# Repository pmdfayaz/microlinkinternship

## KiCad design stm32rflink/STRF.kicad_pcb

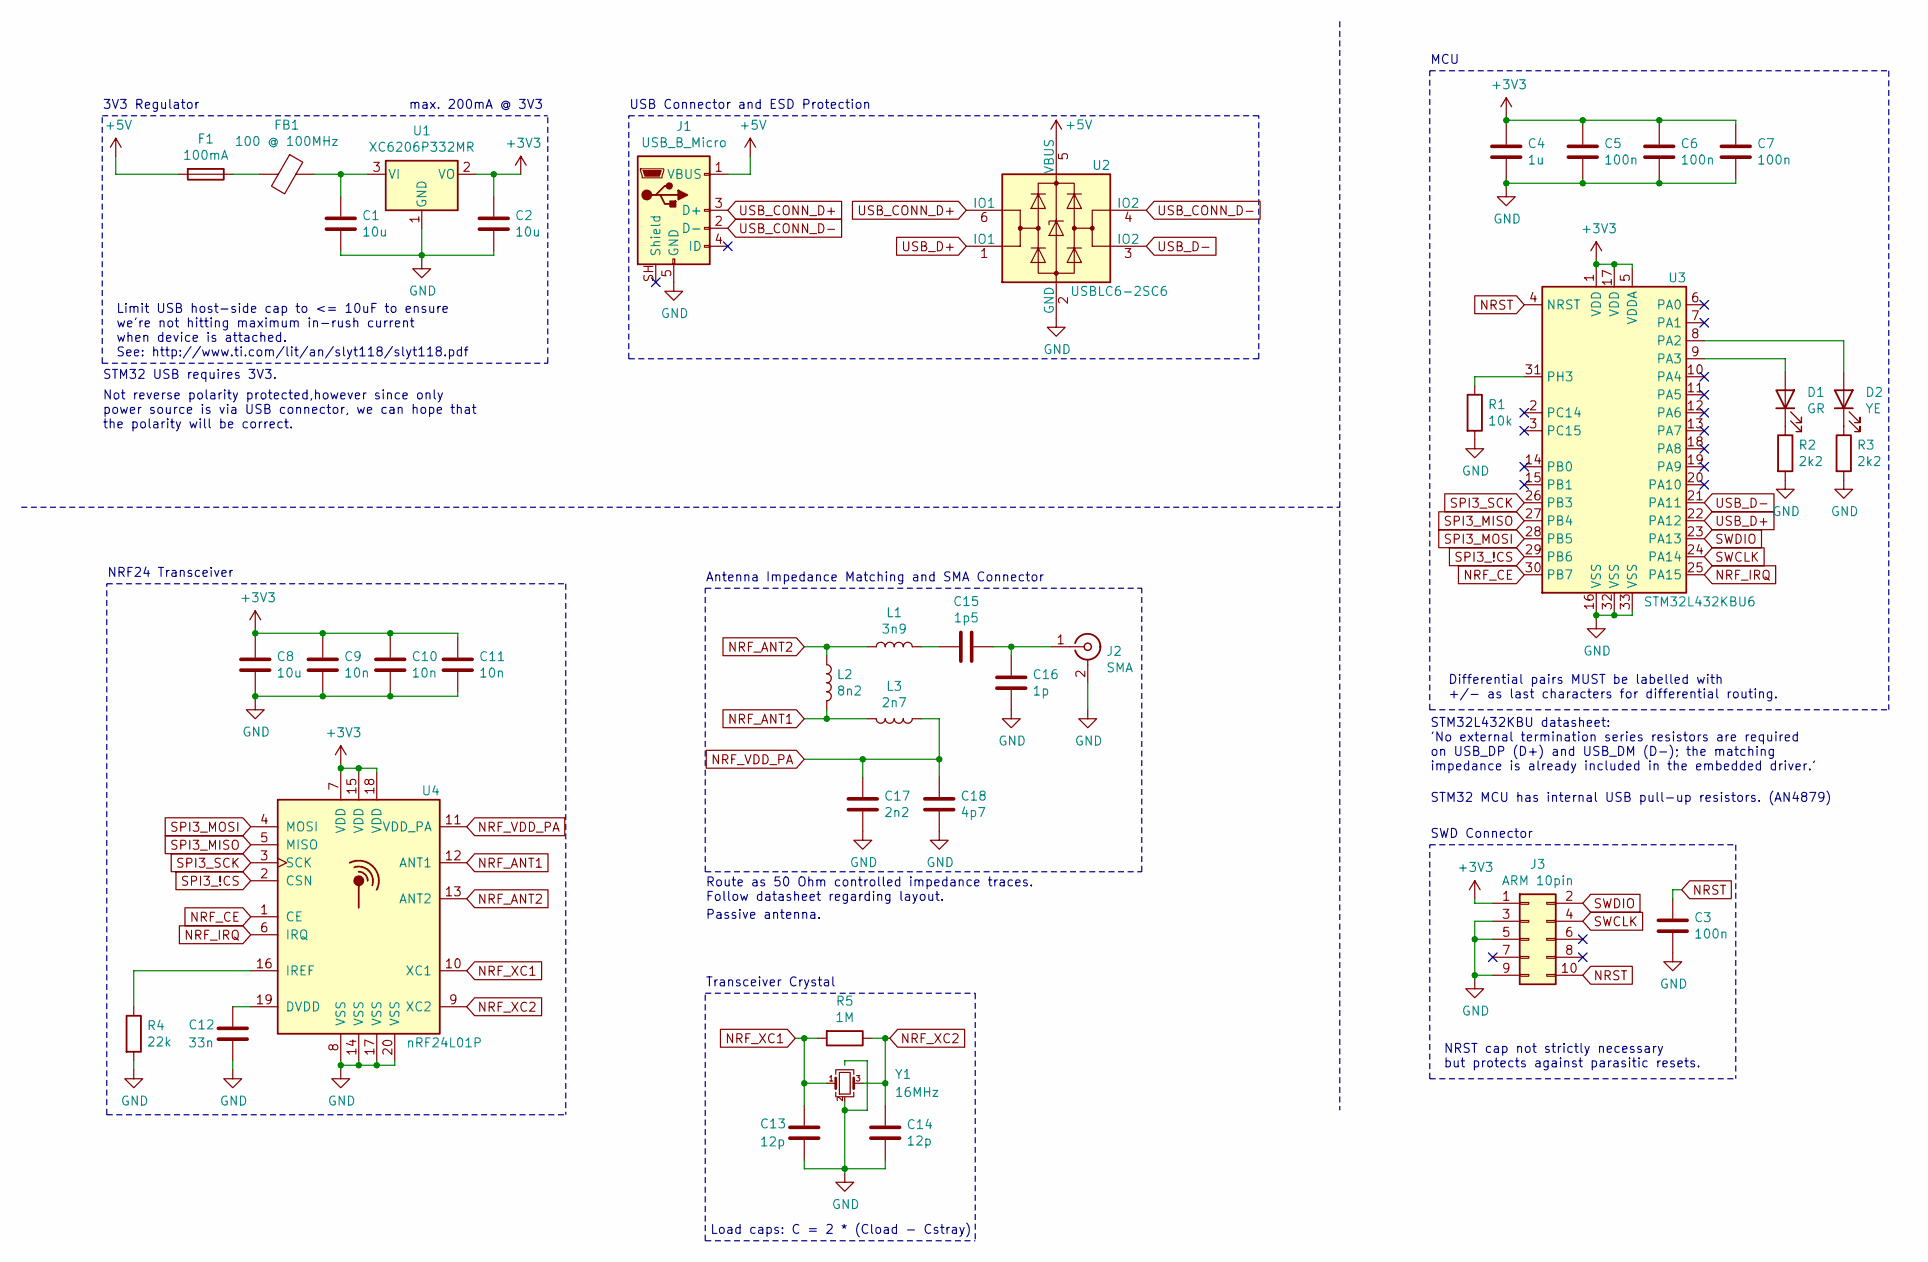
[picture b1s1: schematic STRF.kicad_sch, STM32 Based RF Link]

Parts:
C1, C2, C8: 10u; C_0603_1608Metric
C3, C5, C6, C7: 100n; C_0402_1005Metric
C4: 1u; C_0402_1005Metric
C9, C10, C11: 10n; C_0402_1005Metric
C12: 33n; C_0402_1005Metric
C13, C14: 12p; C_0402_1005Metric
C15: 1p5; C_0402_1005Metric
C16: 1p; C_0402_1005Metric
C17: 2n2; C_0402_1005Metric
C18: 4p7; C_0402_1005Metric
D1: GR; LED_0603_1608Metric
D2: YE; LED_0603_1608Metric
F1: 100mA; Fuse_1206_3216Metric
FB1: 100 @ 100MHz; L_0805_2012Metric
J1: USB_B_Micro; 101181930001LF
J2: SMA; SMA_Samtec_SMA-J-P-X-ST-EM1_EdgeMount
J3: ARM 10pin; PinHeader_2x05_P1.27mm_Vertical
L1: 3n9; L_0402_1005Metric
L2: 8n2; L_0402_1005Metric
L3: 2n7; L_0402_1005Metric
R1: 10k; R_0402_1005Metric
R2, R3: 2k2; R_0603_1608Metric
R4: 22k; R_0402_1005Metric
R5: 1M; R_0402_1005Metric
U1: XC6206P332MR; SOT-23
U2: USBLC6-2SC6; SOT-23-6
U3: STM32L432KBU6; QFN-32-1EP_5x5mm_P0.5mm_EP3.45x3.45mm
U4: nRF24L01P; QFN-20-1EP_4x4mm_P0.5mm_EP2.5x2.5mm
Y1: 16MHz; Crystal_SMD_3225-4Pin_3.2x2.5mm

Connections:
+3V3: C2.1, C4.1, C5.1, C6.1, C7.1, C8.1, C9.1, C10.1, C11.1, J3.1, U1.2 (VO), U3.1 (VDD), U3.5 (VDDA), U3.17 (VDD), U4.7 (VDD), U4.15 (VDD), U4.18 (VDD)
+5V: F1.2, J1.1 (VBUS), U2.5 (VBUS)
GND: C1.2, C2.2, C3.2, C4.2, C5.2, C6.2, C7.2, C8.2, C9.2, C10.2, C11.2, C12.2, C13.2, C14.2, C16.1, C17.1, C18.1, J1.5 (GND), J2.2 (Ext), J3.3, J3.5, J3.9, R1.2, R2.2, R3.2, R4.2, U1.1 (GND), U2.2 (GND), U3.16 (VSS), U3.32 (VSS), U3.33 (VSS), U4.8 (VSS), U4.14 (VSS), U4.17 (VSS), U4.20 (VSS), U4.21, Y1.2 (G), Y1.4 (G)
NRF_ANT1: L2.2, L3.2, U4.12 (ANT1)
NRF_ANT2: L1.1, L2.1, U4.13 (ANT2)
NRF_CE: U3.30 (PB7), U4.1 (CE)
NRF_IRQ: U3.25 (PA15), U4.6 (IRQ)
NRF_VDD_PA: C17.2, C18.2, L3.1, U4.11 (VDD_PA)
NRF_XC1: C13.1, R5.2, U4.10 (XC1), Y1.1
NRF_XC2: C14.1, R5.1, U4.9 (XC2), Y1.3
NRST: C3.1, J3.10, U3.4 (NRST)
unnamed: C1.1, FB1.1, U1.3 (VI)
unnamed: C12.1, U4.19 (DVDD)
unnamed: C15.1, C16.2, J2.1 (In)
unnamed: C15.2, L1.2
unnamed: D1.1 (K), R2.1
unnamed: D1.2 (A), U3.9 (PA3)
unnamed: D2.1 (K), R3.1
unnamed: D2.2 (A), U3.8 (PA2)
unnamed: F1.1, FB1.2
unnamed: R1.1, U3.31 (PH3)
unnamed: R4.1, U4.16 (IREF)
SPI3_!CS: U3.29 (PB6), U4.2 (CSN)
SPI3_MISO: U3.27 (PB4), U4.5 (MISO)
SPI3_MOSI: U3.28 (PB5), U4.4 (MOSI)
SPI3_SCK: U3.26 (PB3), U4.3 (SCK)
SWCLK: J3.4, U3.24 (PA14)
SWDIO: J3.2, U3.23 (PA13)
USB_CONN_D+: J1.3 (D+), U2.6 (IO1)
USB_CONN_D-: J1.2 (D-), U2.4 (IO2)
USB_D+: U2.1 (IO1), U3.22 (PA12)
USB_D-: U2.3 (IO2), U3.21 (PA11)

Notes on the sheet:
NRF24 Transceiver
Transceiver Crystal
STM32 MCU has internal USB pull-up resistors. (AN4879)
max. 200mA @ 3V3
Load caps: C = 2 * (Cload - Cstray)
USB Connector and ESD Protection
MCU
Antenna Impedance Matching and SMA Connector
STM32 USB requires 3V3.
Not reverse polarity protected,however since only power source is via USB connector, we can hope that the polarity will be correct.
Passive antenna.
SWD Connector
Route as 50 Ohm controlled impedance traces. Follow datasheet regarding layout.
3V3 Regulator
STM32L432KBU datasheet: 'No external termination series resistors are required on USB_DP (D+) and USB_DM (D-); the matching impedance is already included in the embedded driver.'
Limit USB host-side cap to <= 10uF to ensure we're not hitting maximum in-rush current when device is attached. See: http://www.ti.com/lit/an/slyt118/slyt118.pdf
NRST cap not strictly necessary but protects against parasitic resets.
Differential pairs MUST be labelled with +/- as last characters for differential routing.

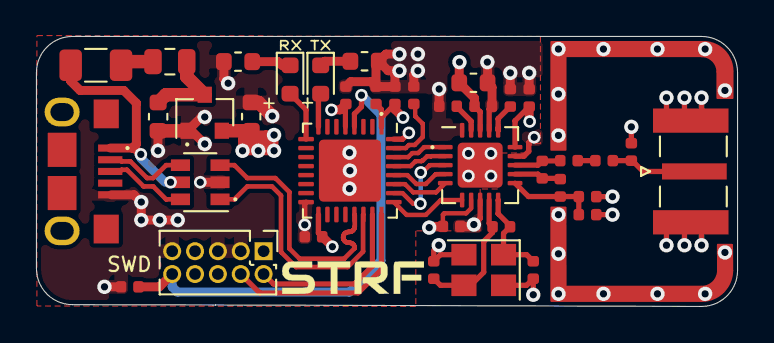
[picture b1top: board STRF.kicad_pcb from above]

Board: 4 copper layers, 39.0 x 15.0 mm, 38 parts (0 on the bottom side), 32 nets.

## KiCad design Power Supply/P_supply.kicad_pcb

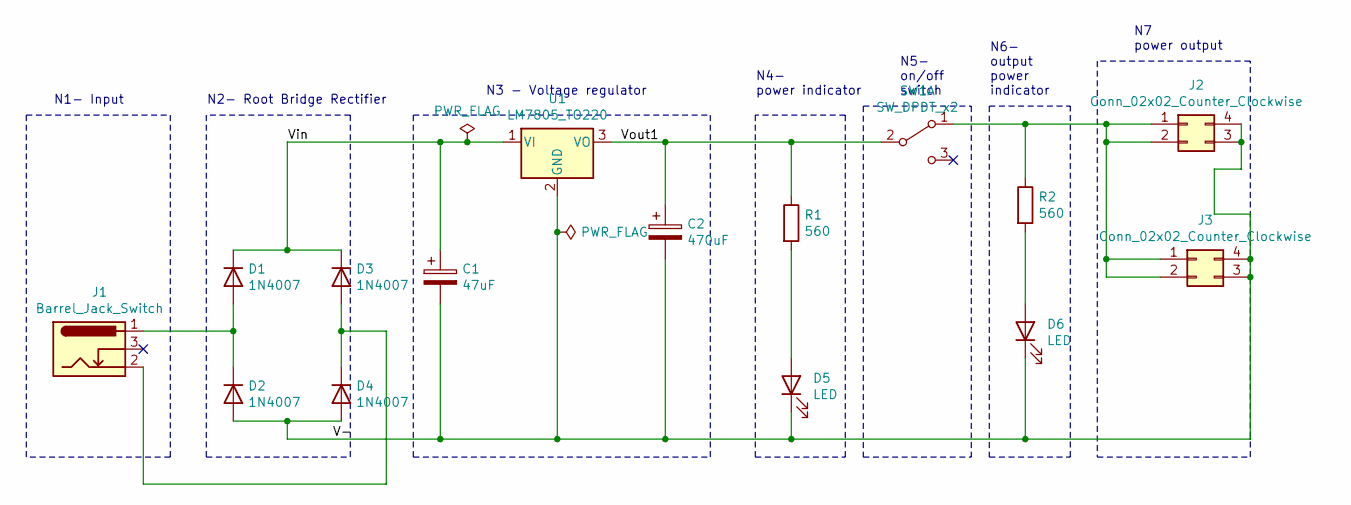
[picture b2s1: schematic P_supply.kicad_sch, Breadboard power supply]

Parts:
C1: 47uF; C_1812_4532Metric
C2: 470uF; C_1812_4532Metric
D1, D2, D3, D4: 1N4007; D_2010_5025Metric
D5, D6: LED; LED_1210_3225Metric
J1: Barrel_Jack_Switch; BarrelJack_CUI_PJ-063AH_Horizontal
J2, J3: Conn_02x02_Counter_Clockwise; PinHeader_2x02_P2.54mm_Vertical
R1, R2: 560; R_1206_3216Metric
SW1: SW_DPDT_x2; SW_E-Switch_EG1224_SPDT_Angled
U1: LM7805_TO220; TO-252-2

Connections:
/V-: C1.2, C2.2, D2.2 (A), D4.2 (A), D5.1 (K), D6.1 (K), J2.3, J2.4, J3.3, J3.4, U1.2 (GND)
/Vin: C1.1, D1.1 (K), D3.1 (K), U1.1 (VI)
/Vout1: C2.1, R1.1, SW1.2 (B), U1.3 (VO)
unnamed: D1.2 (A), D2.1 (K), J1.1
unnamed: D3.2 (A), D4.1 (K), J1.2
unnamed: D5.2 (A), R1.2
unnamed: D6.2 (A), R2.2
unnamed: J2.1, J2.2, J3.1, J3.2, R2.1, SW1.1 (A)

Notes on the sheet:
N7 power output
N6- output power indicator
N3 - Voltage regulator
N1- Input
N2- Root Bridge Rectifier
N4- power indicator
N5- on/off switch

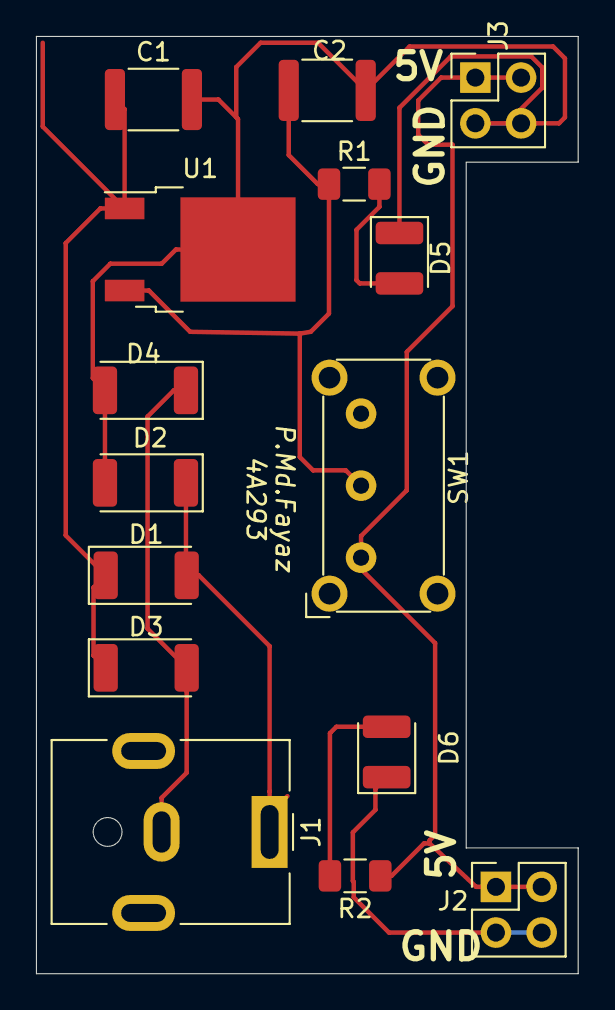
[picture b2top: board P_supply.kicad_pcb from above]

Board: 2 copper layers, 30.1 x 52.1 mm, 15 parts (0 on the bottom side), 8 nets.

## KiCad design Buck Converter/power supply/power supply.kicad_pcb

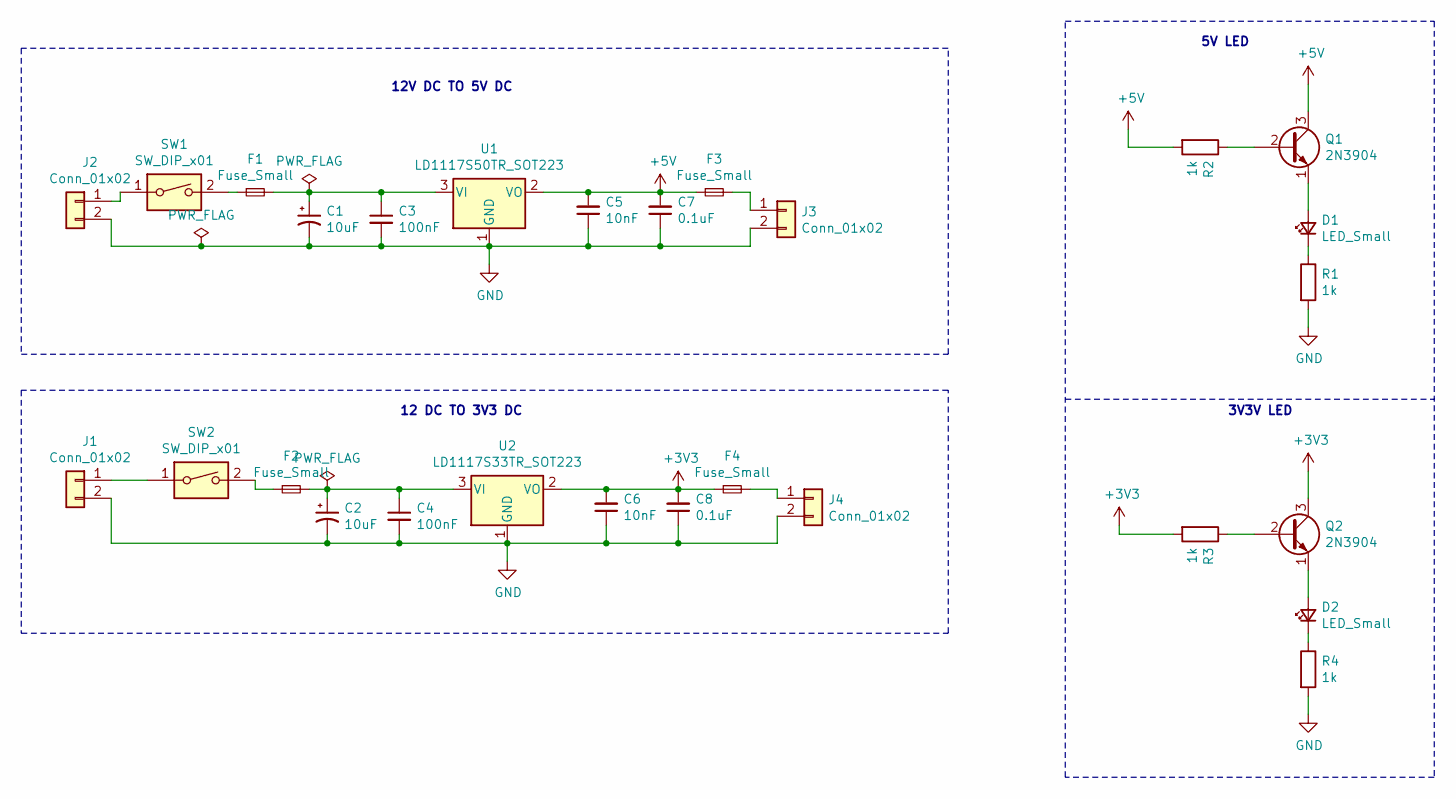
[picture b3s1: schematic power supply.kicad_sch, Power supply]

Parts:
C1, C2: 10uF; C_1206_3216Metric
C3, C4: 100nF; C_1206_3216Metric
C5, C6: 10nF; C_1206_3216Metric
C7, C8: 0.1uF; C_1206_3216Metric
D1, D2: LED_Small; LED_D5.0mm
F1, F2, F3, F4: Fuse_Small; Fuseholder_TR5_Littelfuse_No560_No460
J1, J2, J3, J4: Conn_01x02; Altech_AK300_1x02_P5.00mm_45-Degree
Q1, Q2: 2N3904; TO-92_Inline
R1, R2, R3, R4: 1k; R_1206_3216Metric
SW1, SW2: SW_DIP_x01; SW_DIP_SPSTx01_Piano_10.8x4.1mm_W7.62mm_P2.54mm
U1: LD1117S50TR_SOT223; SOT-223-3_TabPin2
U2: LD1117S33TR_SOT223; SOT-223-3_TabPin2

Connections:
+3V3: C6.2, C8.2, F4.1, Q2.3 (C), R3.2, U2.2 (VO)
+5V: C5.2, C7.2, F3.1, Q1.3 (C), R2.2, U1.2 (VO)
GND: C1.2, C2.2, C3.2, C4.2, C5.1, C6.1, C7.1, C8.1, J1.2, J2.2, J3.2, J4.2, R1.2, R4.2, U1.1 (GND), U2.1 (GND)
unnamed: C1.1, C3.1, F1.2, U1.3 (VI)
unnamed: C2.1, C4.1, F2.2, U2.3 (VI)
unnamed: D1.1 (K), R1.1
unnamed: D1.2 (A), Q1.1 (E)
unnamed: D2.1 (K), R4.1
unnamed: D2.2 (A), Q2.1 (E)
unnamed: F1.1, SW1.2
unnamed: F2.1, SW2.2
unnamed: F3.2, J3.1
unnamed: F4.2, J4.1
unnamed: J1.1, SW2.1
unnamed: J2.1, SW1.1
unnamed: Q1.2 (B), R2.1
unnamed: Q2.2 (B), R3.1

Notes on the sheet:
12V DC TO 5V DC
5V LED
3V3V LED
12 DC TO 3V3 DC

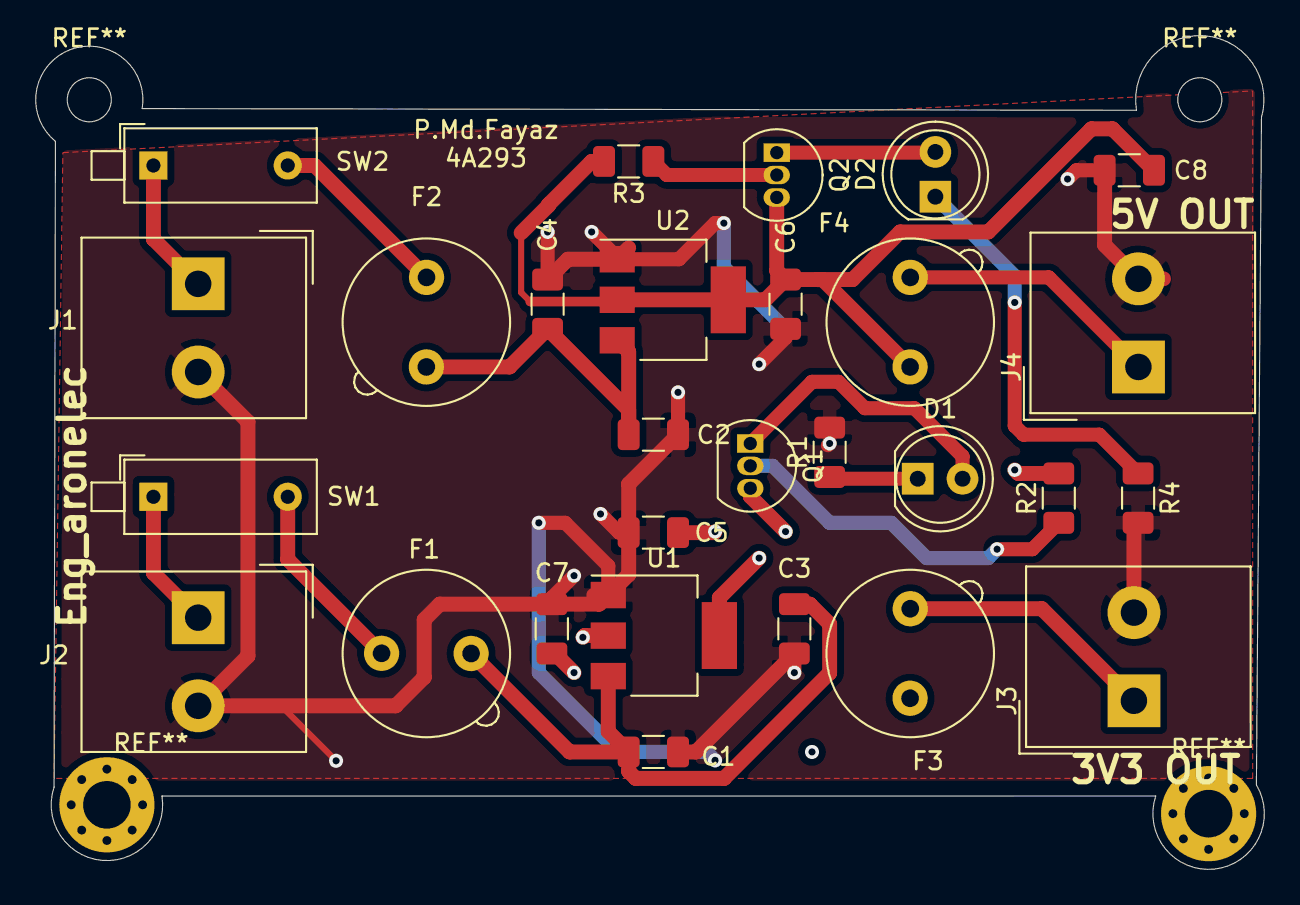
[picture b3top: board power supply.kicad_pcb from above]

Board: 4 copper layers, 69.7 x 47.3 mm, 28 parts (0 on the bottom side), 17 nets.

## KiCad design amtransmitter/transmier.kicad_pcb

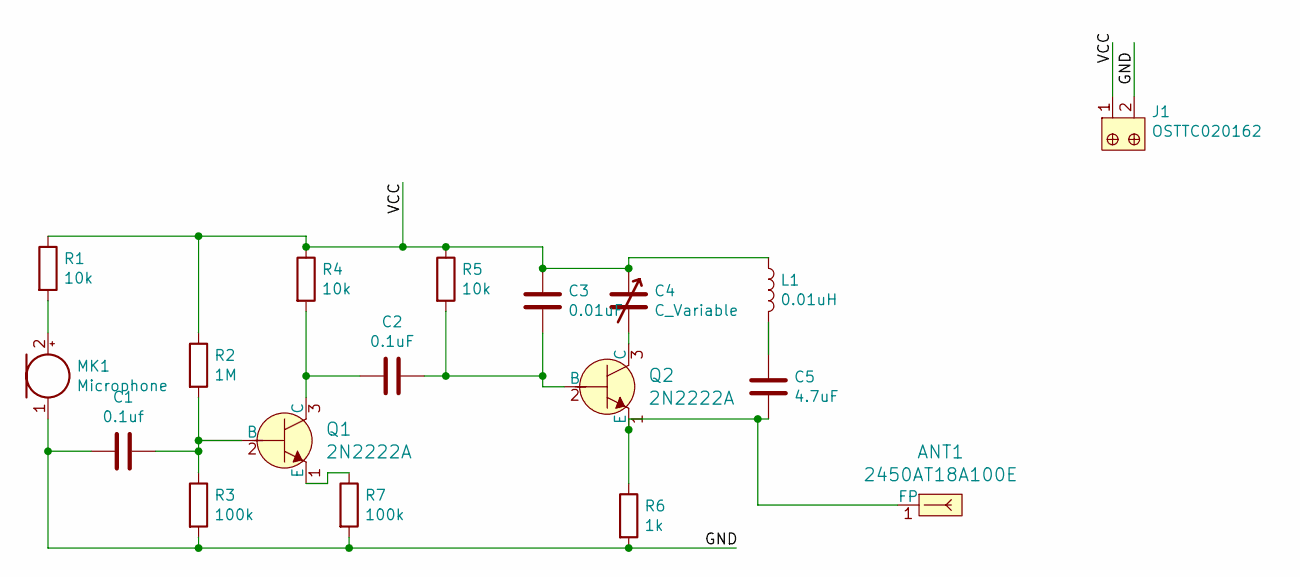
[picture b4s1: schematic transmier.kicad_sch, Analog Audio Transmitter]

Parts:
ANT1: 2450AT18A100E; Pin_D0.9mm_L10.0mm_W2.4mm_FlatFork; MPN 2450AT18A100E; Digi-Key_PN 712-1005-1-ND
C1: 0.1uf; C_Disc_D12.0mm_W4.4mm_P7.75mm
C2: 0.1uF; C_Disc_D12.0mm_W4.4mm_P7.75mm
C3: 0.01uF; C_Disc_D12.0mm_W4.4mm_P7.75mm
C4: C_Variable; C_Rect_L7.0mm_W6.5mm_P5.00mm
C5: 4.7uF; C_Disc_D7.5mm_W5.0mm_P5.00mm
J1: OSTTC020162; C_Disc_D12.0mm_W4.4mm_P7.75mm; MPN OSTTC020162; Digi-Key_PN ED2600-ND
L1: 0.01uH; L_Axial_L14.0mm_D4.5mm_P15.24mm_Horizontal_Fastron_LACC
MK1: Microphone; L_Radial_D10.5mm_P5.00mm_Abacron_AISR-01
Q1, Q2: 2N2222A; TO-18-3; MPN 2N2222A; Digi-Key_PN 2N2222ACS-ND
R1, R4, R5: 10k; R_Axial_DIN0614_L14.3mm_D5.7mm_P15.24mm_Horizontal
R2: 1M; R_Axial_DIN0614_L14.3mm_D5.7mm_P15.24mm_Horizontal
R3, R7: 100k; R_Axial_DIN0614_L14.3mm_D5.7mm_P15.24mm_Horizontal
R6: 1k; R_Axial_DIN0614_L14.3mm_D5.7mm_P15.24mm_Horizontal

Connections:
/GND: C1.2, J1.2, MK1.1 (-), R3.2, R6.2, R7.2
/VCC: C3.2, C4.1, J1.1, L1.1, R1.1, R2.1, R4.1, R5.1
unnamed: ANT1.1 (FP), C5.1, Q2.1 (E), R6.1
unnamed: C1.1, Q1.2 (B), R2.2, R3.1
unnamed: C2.1, C3.1, Q2.2 (B), R5.2
unnamed: C2.2, Q1.3 (C), R4.2
unnamed: C4.2, Q2.3 (C)
unnamed: C5.2, L1.2
unnamed: MK1.2 (+), R1.2
unnamed: Q1.1 (E), R7.1

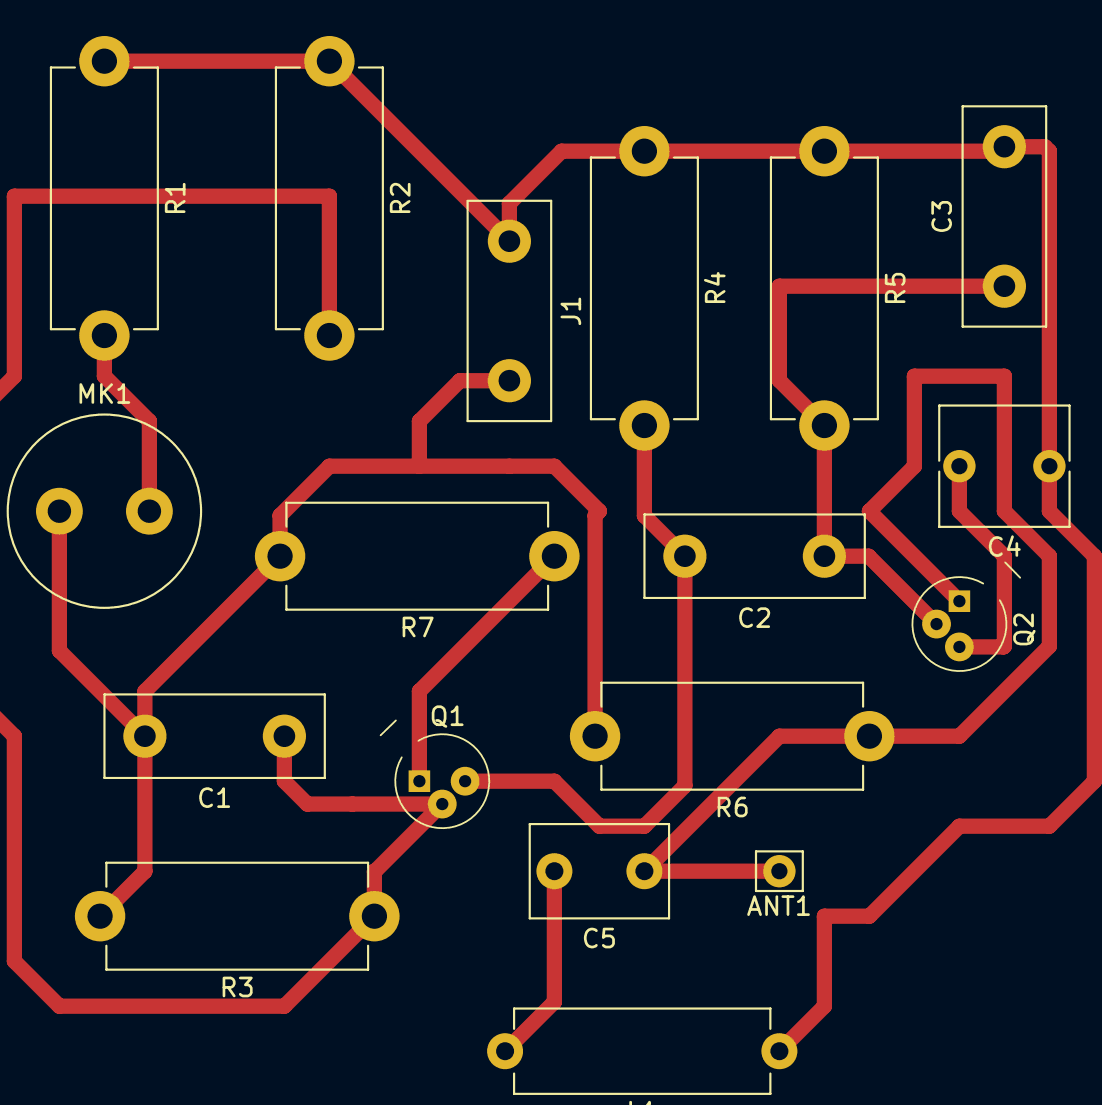
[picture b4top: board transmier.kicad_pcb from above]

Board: 2 copper layers, 18 parts (0 on the bottom side), 10 nets.

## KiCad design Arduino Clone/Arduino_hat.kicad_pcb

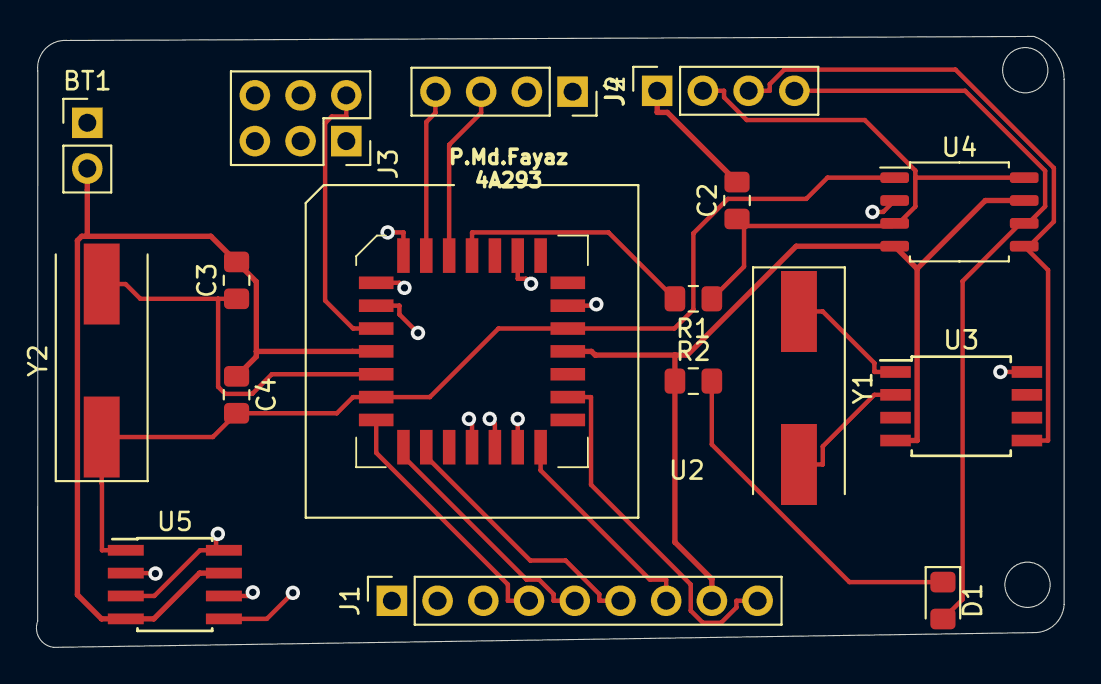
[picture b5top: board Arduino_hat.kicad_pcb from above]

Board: 4 copper layers, 57.1 x 33.9 mm, 17 parts (0 on the bottom side), 22 nets.

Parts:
BT1: 3V; PinHeader_1x02_P2.54mm_Vertical
C2: 10uF; C_0805_2012Metric_Pad1.15x1.40mm_HandSolder
C3, C4: 22pF; C_0805_2012Metric_Pad1.15x1.40mm_HandSolder
D1: LED; LED_0805_2012Metric_Pad1.15x1.40mm_HandSolder
J1: digital pins; PinSocket_1x09_P2.54mm_Vertical
J2: I2C; PinSocket_1x04_P2.54mm_Vertical
J3: ICSP; PinSocket_2x03_P2.54mm_Vertical
J4: serial; PinSocket_1x04_P2.54mm_Vertical
R1: 10Kohm; R_0805_2012Metric_Pad1.15x1.40mm_HandSolder
R2: 330ohm; R_0805_2012Metric_Pad1.15x1.40mm_HandSolder
U2: ATmega328P-PU; PLCC-28_SMD-Socket
U3: DS1337_PDv2; SOIJ-8_5.3x5.3mm_P1.27mm
U4: 24LC1025; SOIC-8_5.275x5.275mm_P1.27mm
U5: 24LC1025; PowerIntegrations_SO-8
Y1: Crystal 32MHz; Crystal_SMD_HC49-SD
Y2: Crystal 16Mhz; Crystal_SMD_HC49-SD

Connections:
/ADDR1: C4.2, U2.10, U2.23, U4.1, U5.1, Y2.1
/ADDR2: U2.24, U4.2, U5.2
/D2: J1.1, U2.4
/D3: J1.2, U2.5
/D4: J1.3, U2.6
/D5: J1.4, U2.11
/D6: J1.5, U2.12
/D7: J1.6, U2.13
/D8: J1.7, U2.18
/MISO: J3.1, U2.16
/MOSI: J3.4, U2.15
/RESET: R1.2, U2.1
/RX: J4.3, U2.2
/SCK: D1.2, J2.4, J3.3, U2.17, U4.6, U5.6
/SDA: J2.3, U2.27, U3.5, U4.5, U5.5
/TX: J4.4, U2.3
/VCC: BT1.1, C2.1, J1.9, J2.2, J3.2, J4.2, R1.1, U2.7, U2.20, U3.8, U4.3, U4.8, U5.3, U5.8
GNDPWR: BT1.2, C2.2, C3.2, C4.1, J1.8, J2.1, J3.6, J4.1, R2.1, U2.8, U2.22, U3.4, U4.4, U4.7, U5.4, U5.7
unnamed: C3.1, U2.9, Y2.2
unnamed: D1.1, R2.2
unnamed: U3.1, Y1.1
unnamed: U3.2, Y1.2
